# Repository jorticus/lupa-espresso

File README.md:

# LUPA ESPRESSO

ESP32 firmware for controlling my modified Vibiemme Domobar Junior, which is an E61-grouphead Heat Exchanger (HX) espresso machine.

The main goal is to add some smarts, but retain the manual control and analog feel.

NOTE: This project is not intended to be re-used on other machines as it is highly specific to the particular modifications I have made.

## Features

- PID control of heater boiler
- Automatic brew timer
- Digital pressure / temperature / flow readouts
- Graphing and gauges displayed on two round TFT displays
- Grouphead temperature approximation
- Preheat/sleep states
- Remote control
- HomeAssistant integration

## Modifications

- Analog pressure dials replaced with round TFT displays
- Digital pressure transducer
- Water flow sensor
- Platinum PT100 thermocouple probe
- Boiler SSR controlled by ESP32

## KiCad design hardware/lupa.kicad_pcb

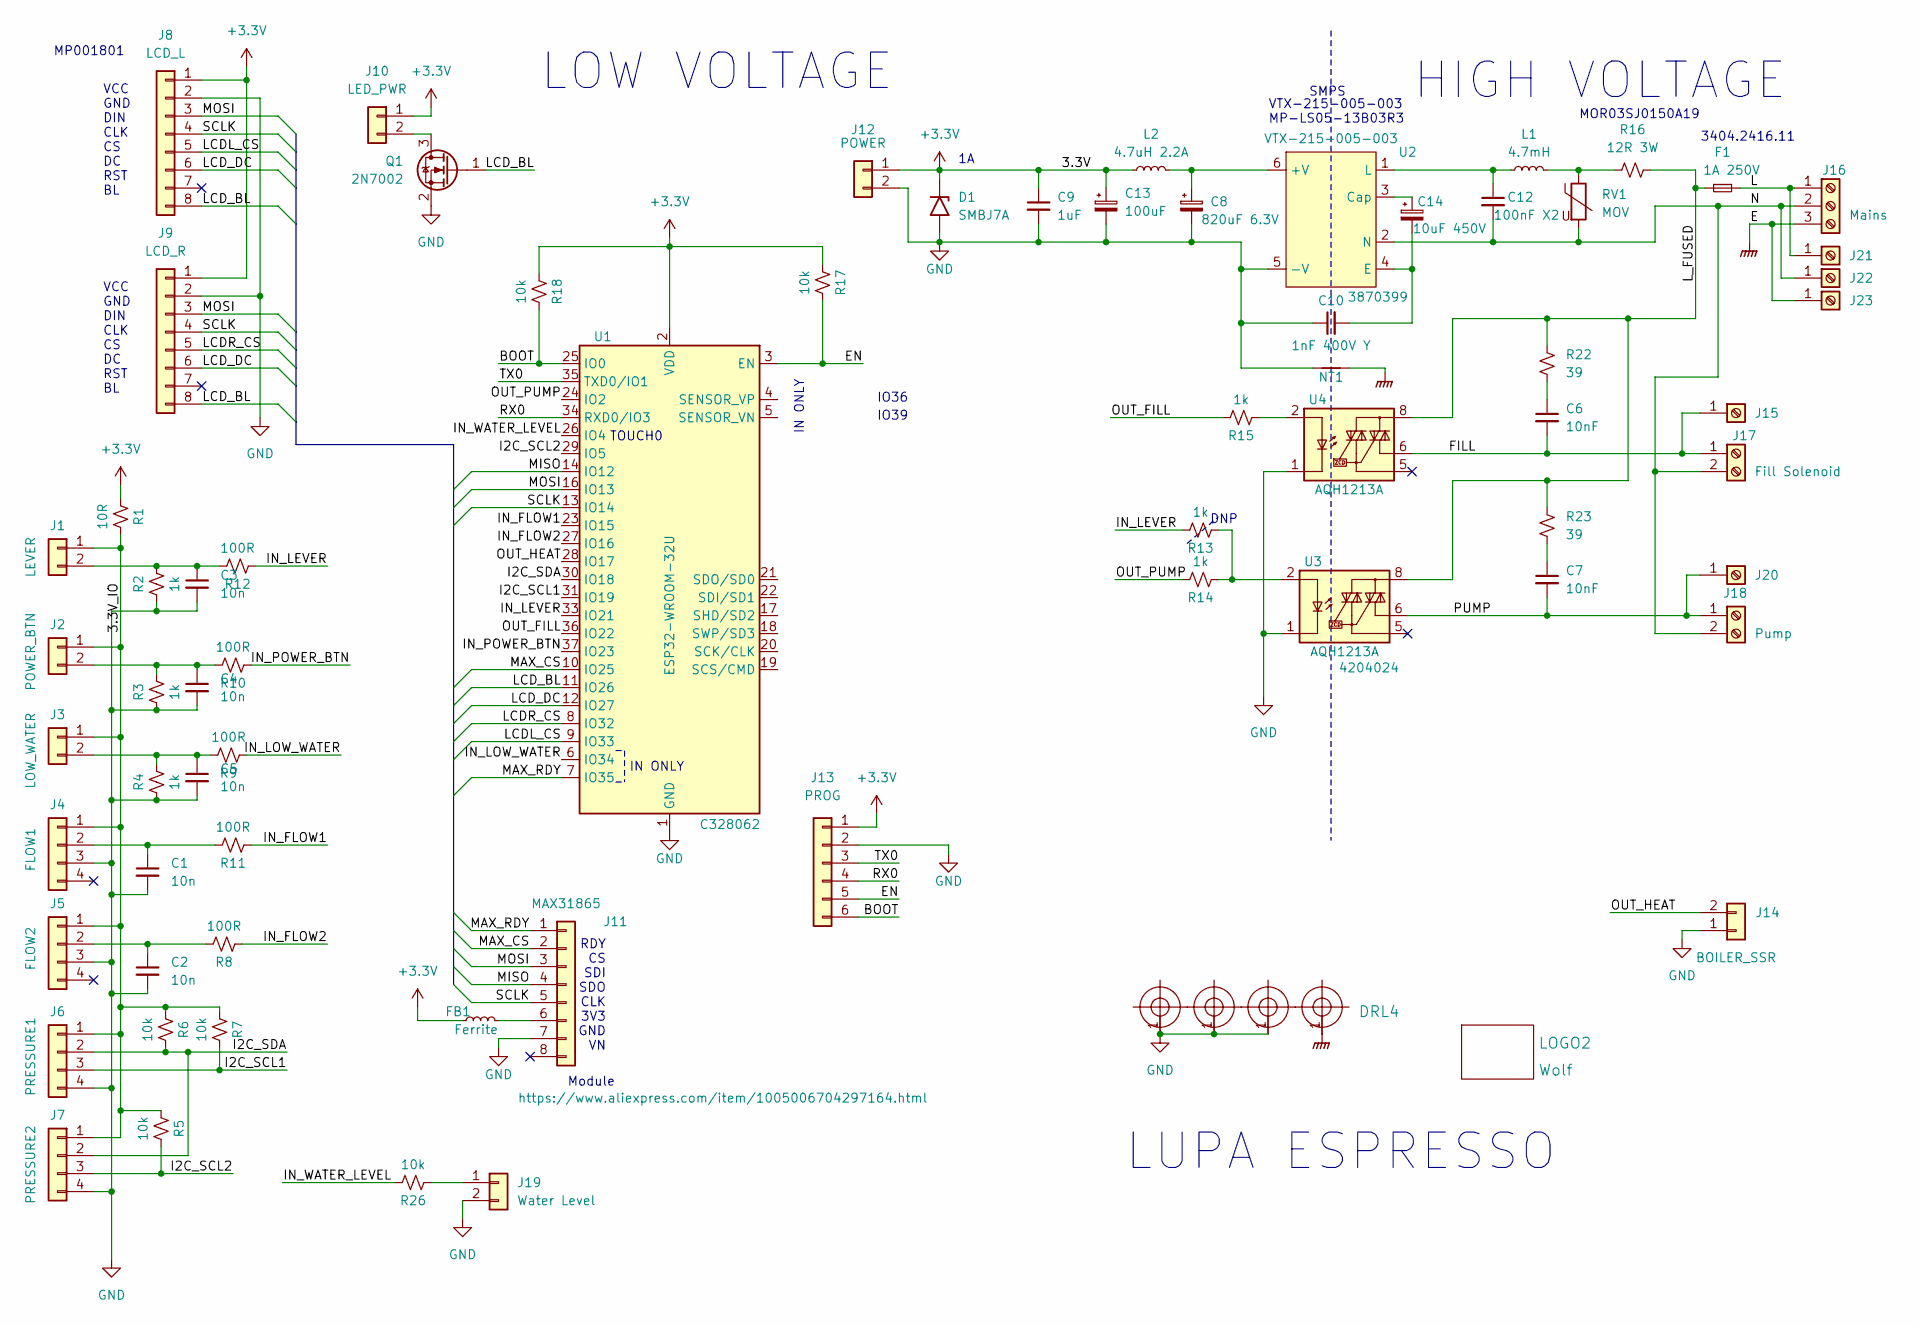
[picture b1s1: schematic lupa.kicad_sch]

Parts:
C1, C2, C3, C4, C5: 10n; C_0603_1608Metric
C6, C7: 10nF; R_0805_2012Metric
C8: 820uF 6.3V; CP_Radial_D8.0mm_P3.50mm; Farnell 2614008
C9: 1uF; C_0603_1608Metric
C10: 1nF 400V Y; C_Rect_L7.0mm_W2.5mm_P5.00mm
C12: 100nF X2; C_Disc_D4.7mm_W2.5mm_P5.00mm
C13: 100uF; CP_Radial_D5.0mm_P2.50mm
C14: 10uF 450V; CP_Radial_D10.0mm_P5.00mm; Farnell 2610819
D1: SMBJ7A; D_SMB
DRL1, DRL2, DRL3, DRL4: DrillHoleE; MountingHole_3.2mm_M3_Pad
F1: 1A 250V; Fuse_Schurter_UMZ250; Farnell 1829461
FB1: Ferrite; R_0603_1608Metric
J1: LEVER; JST_XH_B2B-XH-A_1x02_P2.50mm_Vertical; Farnell 3287572
J2: POWER_BTN; JST_XH_B2B-XH-A_1x02_P2.50mm_Vertical; Farnell 3287572
J3: LOW_WATER; JST_XH_B2B-XH-A_1x02_P2.50mm_Vertical; Farnell 3287572
J4: FLOW1; JST_XH_B4B-XH-A_1x04_P2.50mm_Vertical; Farnell 3287574
J5: FLOW2; JST_XH_B4B-XH-A_1x04_P2.50mm_Vertical; Farnell 3287574
J6: PRESSURE1; JST_XH_B4B-XH-A_1x04_P2.50mm_Vertical; Farnell 3287574
J7: PRESSURE2; JST_XH_B4B-XH-A_1x04_P2.50mm_Vertical; Farnell 3287574
J8: LCD_L; JST_XH_B8B-XH-A_1x08_P2.50mm_Vertical; Farnell 3287578
J9: LCD_R; JST_XH_B8B-XH-A_1x08_P2.50mm_Vertical; Farnell 3287578
J10: LED_PWR; JST_XH_B2B-XH-A_1x02_P2.50mm_Vertical; Farnell 3287572
J11: MAX31865; PinHeader_1x08_P2.54mm_Vertical
J12: POWER; JST_XH_B2B-XH-A_1x02_P2.50mm_Vertical; Farnell 3287572
J13: PROG; PinHeader_1x06_P2.54mm_Vertical_SMD_Pin1Left
J14: BOILER_SSR; JST_XH_S2B-XH-A_1x02_P2.50mm_Horizontal; Farnell 3287588
J15, J20, J21, J22, J23: Screw_Terminal_01x01; TAB_TERMINAL
J16: Mains; Altech_AK300_1x03_P5.00mm_45-Degree
J17: Fill Solenoid; Altech_AK300_1x02_P5.00mm_45-Degree
J18: Pump; Altech_AK300_1x02_P5.00mm_45-Degree
J19: Water Level; JST_XH_B2B-XH-A_1x02_P2.50mm_Vertical; Farnell 3287572
L1: 4.7mH; L_Radial_D6.0mm_P4.00mm
L2: 4.7uH 2.2A; L_6.3x6.3_H3
LOGO2: Wolf; wolfpaw-0.3
NT1: NetTie_2; NetTie-2_SMD_Pad2.0mm
Q1: 2N7002; SOT-23
R1: 10R; R_0603_1608Metric
R2, R3, R4, R13, R14, R15: 1k; R_0603_1608Metric
R5, R6, R7, R17, R18, R26: 10k; R_0603_1608Metric
R8, R9, R10, R11, R12: 100R; R_0603_1608Metric
R16: 12R 3W; R_Axial_DIN0516_L15.5mm_D5.0mm_P5.08mm_Vertical; Farnell 1357899
R22, R23: 39; R_0805_2012Metric
RV1: MOV; C_Disc_D4.7mm_W2.5mm_P5.00mm
U1: ESP32-WROOM-32U; LCSC C328062
U2: VTX-215-005-003; SMPS-VTX-215-005-003; Farnell 3870399
U3, U4: AQH1213A; SSO-7-8_6.4x9.78mm_P2.54mm; Mouser 769-AQH1213A

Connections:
+3.3V: C9.1, C13.1, D1.1 (A1), FB1.1, J8.1, J9.1, J10.1, J12.1, J13.1, L2.1, R1.1, R17.1, R18.1, U1.2 (VDD)
/3.3V_IO: J1.1, J2.1, J3.1, J4.1, J5.1, J6.1, J7.1, R1.2, R5.1, R6.1, R7.1
/BOOT: J13.6, R18.2, U1.25 (IO0)
/EN: J13.5, R17.2, U1.3 (EN)
/FILL: C6.2, J15.1, J17.1, U4.6
/I2C_SCL1: J6.3, R7.2, U1.31 (IO19)
/I2C_SCL2: J7.3, R5.2, U1.29 (IO5)
/I2C_SDA: J6.2, J7.2, R6.2, U1.30 (IO18)
/IN_FLOW1: R11.1, U1.23 (IO15)
/IN_FLOW2: R8.1, U1.27 (IO16)
/IN_LEVER: R12.1, R13.2, U1.33 (IO21)
/IN_LOW_WATER: R9.1, U1.6 (IO34)
/IN_POWER_BTN: R10.1, U1.37 (IO23)
/IN_WATER_LEVEL: R26.2, U1.26 (IO4)
/L: F1.2, J16.1, J21.1
/LCDL_CS: J8.5, U1.9 (IO33)
/LCDR_CS: J9.5, U1.8 (IO32)
/LCD_BL: J8.8, J9.8, Q1.1 (G), U1.11 (IO26)
/LCD_DC: J8.6, J9.6, U1.12 (IO27)
/L_FUSED: F1.1, R16.2, R22.1, R23.1, U3.8, U4.8
/MAX_CS: J11.2, U1.10 (IO25)
/MAX_RDY: J11.1, U1.7 (IO35)
/MISO: J11.4, U1.14 (IO12)
/MOSI: J8.3, J9.3, J11.3, U1.16 (IO13)
/N: C12.2, J16.2, J17.2, J18.2, J22.1, RV1.2, U2.2 (N)
/OUT_FILL: R15.2, U1.36 (IO22)
/OUT_HEAT: J14.2, U1.28 (IO17)
/OUT_PUMP: R14.2, U1.24 (IO2)
/PUMP: C7.2, J18.1, J20.1, U3.6
/RX0: J13.4, U1.34 (RXD0/IO3)
/SCLK: J8.4, J9.4, J11.5, U1.13 (IO14)
/TX0: J13.3, U1.35 (TXD0/IO1)
GND: C1.2, C2.2, C3.2, C4.2, C5.2, C8.2, C9.2, C10.1, C13.2, D1.2 (A2), DRL1.1, DRL2.1, DRL3.1, J4.3, J5.3, J6.4, J7.4, J8.2, J9.2, J11.7, J12.2, J13.2, J14.1, J19.2, NT1.1, Q1.2 (S), R2.1, R3.1, R4.1, U1.1 (GND), U1.15 (GND), U1.38 (GND), U1.39 (GND), U2.5 (-V), U3.1, U3.3, U3.4, U4.1, U4.3, U4.4
GNDPWR: DRL4.1, J16.3, J23.1, NT1.2
unnamed: C6.1, R22.2
unnamed: C7.1, R23.2
unnamed: C3.1, J1.2, R2.2, R12.2
unnamed: C4.1, J2.2, R3.2, R10.2
unnamed: C5.1, J3.2, R4.2, R9.2
unnamed: C1.1, J4.2, R11.2
unnamed: C2.1, J5.2, R8.2
unnamed: J10.2, Q1.3 (D)
unnamed: FB1.2, J11.6
unnamed: J19.1, R26.1
unnamed: L1.2, R16.1, RV1.1
unnamed: R13.1, R14.1, U3.2
unnamed: R15.1, U4.2
unnamed: C8.1, L2.2, U2.6 (+V)
unnamed: C14.1, U2.3 (Cap)
unnamed: C10.2, C14.2, U2.4 (E)
unnamed: C12.1, L1.1, U2.1 (L)

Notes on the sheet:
HIGH VOLTAGE
Module
LOW VOLTAGE
MOR03SJ0150A19
IN ONLY
RDY CS SDI SDO CLK 3V3 GND VN
TOUCH0
MP001801
SMPS
VCC GND DIN CLK CS DC RST BL
LUPA ESPRESSO
VTX-215-005-003 MP-LS05-13B03R3
DNP
IO39
IO36
3404.2416.11

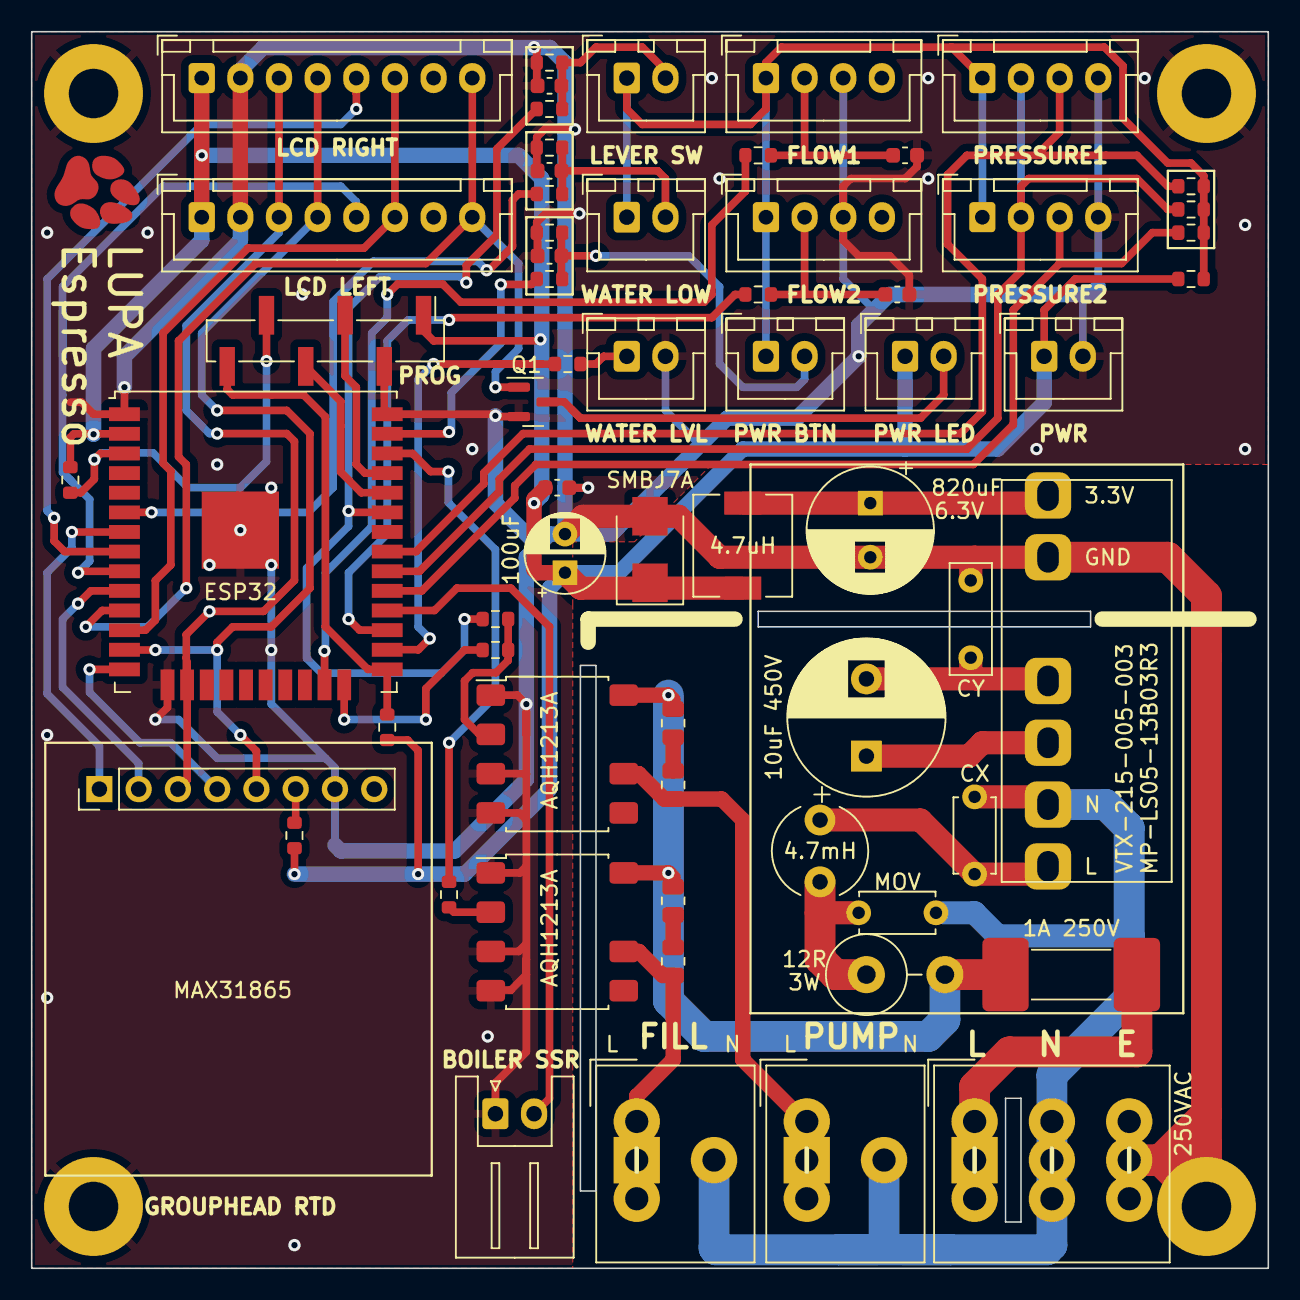
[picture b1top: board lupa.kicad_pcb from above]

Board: 2 copper layers, 80.0 x 80.0 mm, 74 parts (0 on the bottom side), 51 nets.

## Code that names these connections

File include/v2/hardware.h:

#pragma once

//
// Input GPIOs
//

// Lever actuator input switch
// High = Lever open
// Low  = Lever closed or partially open
#define PIN_IN_LEVER 8

// Water tank low switch
// High = Water tank is low
//#define PIN_IN_WATER_LOW 22
#define PIN_IN_WATER_LOW 9

// Power button
#define PIN_IN_POWER_BTN 10

// Water flow pulse sensor input pin
// 5V-24V
// Pull-up
// Flow rate 0.75-1L/min
// https://www.eptsensor.com/flow-sensor/hall-flow-sensor/fm-hl3012-flow-meter-hall-sensor.html
#define FLOW1_PULSE_PIN 11
#define FLOW2_PULSE_PIN 12
// Note: D39 has stability issues, do not use for this.

// Boiler tank sensor (capsense/touch)
// Used for auto-fill logic
#define PIN_IN_WATER_FULL 4 // Touch0

//
// Output GPIOs
//

// Boiler heater element output (PWM)
#define PIN_OUT_HEAT 13

// Pump output (PWM)
#define PIN_OUT_PUMP 14

// Fill boiler solenoid output (On/Off)
//#define PIN_OUT_FILL_SOLENOID 5
#define PIN_OUT_FILL_SOLENOID 45


//
// I2C Bus
//
// [0x7F] : Pressure Transducer
//
#define I2C_SCL     46
#define I2C_SDA     47
//#define I2C_SCL1     46
#define I2C_SCL2     48 // 2nd transducer, shares SDA

// Pressure Transducer
// White: SDA
// Black: SCL
// Brown: 3.3V
// Blue:  GND
#define PRESSURE_I2C_ADDR (0x7F)

// Full-scale pressure reading
// Note: even though full scale pressure is 12 bar, 
// the actual full scale is 120 units.
// Pressure should read 1.0 bar when open to atmosphere.
#define PRESSURE_FULL_SCALE (120) // Bar x10


//
// SPI Bus 1 (HSPI)
// - LCD Left & Right
// SPI Bus 2 (VSPI)
// - MAX31865 RTD #1 & #2
//

#define MAX_RDY     40

#define MAX1_CS     38
#define MAX2_CS     39

#define RTD_NOMINAL_RESISTANCE (100)
#define RTD_REFERENCE_RESISTANCE (430)
#define RTD_MIN_TEMP (-200)
#define RTD_MAX_TEMP (400)


#define LEDC_CH_DISPLAY (0)
#define LEDC_CH_PUMP    (2)

#define UART_DEBUG_BAUD (115200)

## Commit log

2023-05-09 Improve MAX RTD conversion speed
2023-05-09 Implement pulse counting
2023-05-10 Move to TFT_eSPI and implement double buffering to prevent flicker
2023-05-11 Add RST pin for TFT
2023-05-16 Flesh out UI and core state machine
2023-05-16 Update hardware - protoboard design with 2 displays
2023-05-16 Fix MAX SPI configuration, detect non-responsive sensor
2023-05-16 Update I2C configuration to avoid use of GPIO2, as this causes problems with flashing
2023-05-16 Update HW configuration
2023-05-16 Implement WiFi & OTA
2023-05-17 Improve water flow readings, fix pressure scale
2023-05-17 Filter pressure/temperature samples with FIR filter
2023-05-17 Update filters and improve pressure reading responsiveness
2023-05-17 Increase clock for TFT
2023-05-17 Rename PressureTransducer.h
2023-05-17 Double TFT clock rate again, 33ms update
2023-05-17 Add gauges to sensor test view and adjust colors
2023-05-17 Update FIR filter taps to have a cleaner impulse response
2023-05-17 Fix graphing
2023-05-17 Rework UI and detect lever pull from water flow sensor
2023-05-20 Calibrate thermocouple and provide grouphead estimate
2023-05-20 Improve temperature reading stability
2023-05-20 Implement PID control of boiler
2023-05-20 Re-architect code
2023-05-21 Update PID parameters
2023-05-21 Update UI element placement
2023-05-21 Debounce brew timer
2023-05-21 Add steam and sleep modes
2023-05-21 Fix sleep idle timeout
2023-05-21 Fix temperature sensor glitching
2023-05-26 Configure device to not go to sleep after preheating
2023-05-26 Apply offset to heater PID when water is flowing
2023-05-26 Resume preheat cycle if waking from sleep
2023-05-26 Add README and LICENSE
2023-05-28 Implement new PID algorithm
    - Uses floats
    - Allows perturbation of error to provide manual prediction
    - Caller is now responsible for calling at a regular tick rate (fits better with my architecture)
2023-06-05 WiFi no longer blocks initialization
2023-06-05 Add HomeAssistant support for remote on/off and sensor reporting
2023-06-05 Simplify usage of HAComponent
2023-06-05 Fix OTA not turning on LCD
2023-06-05 Continue reporting temperature when off
2023-06-11 Refactor code
2023-06-11 Implement power button
2023-06-11 Add WiFi reconnection logic
2023-06-11 Estimate boiler power draw and report to HomeAssistant
2023-06-11 Fix sleep mode timeout
2023-06-12 Cleanup
2023-06-12 Refactor UI code structure
2023-06-12 Fix bad state logic
2023-06-12 Implement power off/on animation
2023-06-13 Rename HeatControl::setMode to setProfile, reorganize heat profile config
2023-06-13 Filter flowrate and rework SensorSampler
2023-06-13 Add PID tuning mode, fix bug where heater gets stuck on at 1% power
2023-06-13 Disable MQTT publish debug statements
2023-06-13 Improve tuning algorithm
2023-07-10 Add second flow meter and calibrate flow readings
2023-07-10 Detect firmware crash from reset reason
2023-07-12 Update for Rev1 hardware
2023-07-12 Implement hardware pump and water fill control
2023-07-12 Tidy up pump / fill logic state machine
2023-07-12 Rewrite state machine core
2023-07-12 Add linear dimming LUT for fade in/out anim
2023-07-12 Set power-on state to off
2023-07-12 Disable WiFi power saving to improve connection reliability
2023-09-25 Enable task watchdog
2023-09-25 Fix automatic water fill causing preheat state to exit early
2023-09-25 Update water level thresholds
2023-09-25 Enable PSRAM workarounds to attempt to fix crashing
2023-09-25 Update default boiler temperature presets
2023-09-25 Move preheat done check to Sensor Sampler
    Eventually will make this detect whether the temperature has stabilized
2023-09-25 Disable PID perturbation as it is making the PID overshoot too much
2023-10-02 Turn off water level sensor in standby to prevent corrosion of metal probe
2023-12-01 Experiment in attempt to isolate crashes
2023-12-01 Undo experiment
2023-12-01 Fix pump not turning off when tank runs empty
2023-12-01 Fix display turning off if power button pressed rapidly
2023-12-01 Implement pressure stabilization routine to keep water loop filled
2023-12-02 Report pressure sensor to HomeAssistant, change sample rate to 5s
2024-01-26 Fix crash due to timer reset
2024-01-26 Fix brightness animation during fault
2024-01-26 Use both pulse counters
2024-01-26 Improve WiFi reconnect robustness
2024-01-27 Add fault diagnostics
2024-01-27 Actually fix crash due to timer not rearming
    Somehow calling touch_pad_filter_stop() interferes with the FreeRTOS timer queue, preventing the SensorSampler timer from being able to be re-armed.
2024-03-22 Fix watchdog triggering on startup if init takes too long
2024-03-22 Fix water tank low signal being unstable while reading RTD sensor
2024-03-22 Fix glitches in display brightness during power on/off animation
2024-03-22 Fix boiler low signal briefly asserting during power on
2024-03-22 Disable internal temperature sensor reading, it is not useful
2024-03-22 Add vscode extension recommendations
2024-03-22 Add pressure PID control
2024-03-23 Fine tune PID algorithm to ensure stable control of pump pressure
2024-03-23 Add failsafe recovery path since I'm so good at finding fatal bugs in the ESP32
2024-03-23 Add copy of schematic
2024-03-24 Tidy up MQTT config parameters and pump control code
2024-03-24 Don't transition from Sleep->Preheat/Ready with isBrewing
2024-03-24 Fix MQTT causing watchdog timeout when server is unreachable
2024-03-24 Ensure fault UI is shown in failsafe mode
2024-03-24 Reduce spam
2024-03-24 Improve fault/recovery logic and show recovery UI
2024-03-24 Disable PCNT timer as it causes severe issues (when I least expect it)
2024-03-24 Fix MQTT parameter constructor order
2024-03-24 Fix error when trying to set pump state before LEDC is initialized
2024-03-24 Clean up HeatController and move PWM to IO namespace
2024-03-24 Restrict PID integral accumulator when output is being driven negative
2024-03-24 Add config parameters for target temp/pressure
2024-03-24 Redirect debug logging to telnet
2024-05-03 Fix pulsing animation
2024-05-03 Update default PID coefficients for boiler
2024-05-03 Update UI strings for WiFi
2024-05-06 Fix watchdog crash when MQTT server is not available
    The DNS lookup for the MQTT server hostname has a timeout of 15 seconds, which exceeds the watchdog timeout. The loop now returns immediately (timeout of 0) to prevent blocking if the hostname isn't 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
2024-05-06 Avoid calling network tasks if WiFi is not connected
2024-06-03 Change temperature defaults for better brew
2024-06-08 Reenable perturbation when pulling shot
2024-06-08 Disable steam mode for testing purposes
2024-06-08 Fix flow rate measurement
2024-06-09 Add second RTD sensor to measure main boiler
2024-06-09 Debounce water tank low input
2024-06-10 Clean up reconnection logic and add fallback AP mode
2024-06-10 Add a second derivative term using the boiler, to compensate for steam
2024-06-10 Display PID terms on display graph for debug
2024-06-10 Fix heater output ceasing to function
2024-07-08 Fix glitch in boiler PWM output
2024-07-09 Add LVGL image generation build step
2024-07-09 Improve failsafe handling
2024-07-09 Add icons for wifi status and background image
    NOTE: background image reduces framerate quite a bit, may need to remove for performance.
2024-07-09 Attempt to force wifi reconnect if stuck in idle for too long
2024-07-09 Add more icons, tidy up
2024-09-11 Address watchdog timeouts due to WiFiClient timeout
2024-11-29 Update default PID parameters
2024-11-29 Update background image, optimize byte order
2024-11-29 Split work into RTOS tasks
2024-11-29 Clear fault after timeout
2024-11-29 Fix invalid power meter readings
2024-11-29 Formatting
2024-11-29 Add web server
2024-12-22 Prevent message from being repeatedly printed to debug port
2024-12-23 Stop background work when in OTA mode
2024-12-23 Retain MQTT parameter topics
2024-12-23 Serve static HTML for web dashboard (buggy)
2024-12-23 Fix pump sometimes not triggering when lever pulled
2024-12-24 Tidy up UI
2024-12-24 Idle timeout turns off machine
2025-12-01 Pin package versions, improve missing sensor handling, update comments
2025-12-01 Add PCB design files
2025-12-01 Update BOM
2025-12-01 Add component sourcing information
2026-01-16 Migrate to Arduino Core 3.x, add support for ESP32-S3 board
2026-01-18 Minimal functionality working on ESP32-S3
    Webserver disabled due to crash, sensors not yet tested
2026-01-20 Use board variants for IO pin mapping, compiles now for both variants
2026-01-20 Update filling animation to show a wavey tank
2026-01-20 Implement brew profiling logic
    Supports code-defined brewing profiles for both pressure and flow-rate regulated modes
2026-01-20 Fix compiler warnings
2026-01-21 Fix issues running on LupaV1
2026-01-22 Fix partition table for LupaV1 (Using N4 variant)
2026-01-22 Improve web server, home assistant integration, and brew profiles
    Brew profile can now be selected via HA
2026-01-22 Fix heater not turning off edge case
2026-01-23 Plumbing for brew profiles
2026-01-23 Minor improvements
2026-01-23 Replace usage of Wire.h with native ESP I2C driver
2026-01-23 Rework web interface and optimize memory usage
2026-01-24 Rework web interface again (mongoose server, uPlot charting) - finally reliable!
2026-01-24 Add heap logging to track down allocations
2026-01-24 Rework sensor sampler for better sampling reliability
    Moved all sampling out of timers into a dedicated high priority task -
    this works much better and ensures other tasks won't block sampling
2026-01-25 Remove hacomponent submodule
2026-01-27 Revamp Brew control loop - no longer using PID, more stable
2026-01-27 Tidy up Brew Control loop and metric reporting
2026-01-27 Rework display update to work with reduced RAM
    Something changed in Arduino 3.x.x and now there is no longer enough heap to allocate both buffers without external PSRAM...
    I tried hacking around this, but it caused severe stability problems in the ESP stack.
    So, the only alternatives are to either use a PSRAM part or only use one buffer and alternate between drawing left & right.
